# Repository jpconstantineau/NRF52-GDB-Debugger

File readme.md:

# NRF52-GDB-DEBUGGER

## Why?

### Software
This SWD Programmer gets rid of intermediate programs like OpenOCD, STLink server or Segger J-Link.  You just start GNU Debugger (GDB) and select the virtual com port offered by the programmer as your extended remote target.  This means that you only need arm-none-eabi-gdb which is part of the GNU Arm Embedded Toolchain and do not need to install any other software on your computer.  It also means that it's compatible with Windows, Linux and MacOS.

### Hardware
Hardware is compatible with the Version 1 of the [Black Magic Probe](https://github.com/blacksphere/blackmagic). Schematic of the programmer is [here](https://github.com/jpconstantineau/NRF52-GDB-Debugger/blob/master/hardware/bmp/schematic.pdf).  Although you can use an inexpensive Bluepill board and flash the BMP firmware yourself, this programmer adds these features:

* Compatible with native BMP firmware
* Supports 1.8V up to 3.3V targets (TXS0108E level shifter)
* Can provide 3.3V to the target (Mosfet switch)
* 10 pin 0.1" header compatible with the standard Arm Cortex SWD header, including the [TC2050](https://www.tag-connect.com/product/tc2050-idc-nl-10-pin-no-legs-cable-with-ribbon-connector)
* 4 pin 0.1" SWD header, compatible with the BlueMicro840 and BlueMacro840 SWD pads (No need for extra cables to flash bootloader to these boards).
* USB-C Connector

## Firmware
You can follow the instructions on the [BMP Wiki](https://github.com/blacksphere/blackmagic/wiki/Upgrading-Firmware) to update the firmware on the programmer.  You can use the latest [firmware](https://github.com/blacksphere/blackmagic/releases/) and upload the blackmagic-native.bin file contained in the tar.gz file.

On Windows, you may need [Zadig](https://github.com/pbatard/libwdi/releases/download/b730/zadig-2.5.exe) in order for the DFU Utility to detect the programmer.

## Programming the nRF52 using this programmer.

As a starting point, have a look [here](https://bluetun.serverbox.ch/2020/01/10/flashing-the-nrf52840-with-a-blackmagic-probe-swd-jtag-programmer/)

The [Community Add-on to the Adafruit_nRF52_Arduino Board Support Package](https://github.com/jpconstantineau/Community_nRF52_Arduino) has included the Black Magic Probe to the Arduino IDE so that it can be used to program the bootloader. See it in action [here](https://youtu.be/hIclx-_i-jQ)

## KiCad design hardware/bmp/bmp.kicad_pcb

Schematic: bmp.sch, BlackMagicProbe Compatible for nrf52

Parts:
C1, C2: 10uF; C_0603_1608Metric; LCSC C19702
C3, C4: 22pF; C_0603_1608Metric; LCSC C1653
C5, C6, C7, C8: 100nF; C_0603_1608Metric; LCSC C14663
D1: Green - 19-217/GHC-YR1S2/3T; LED_0603_1608Metric; LCSC C72043
D2: Red - KT-0603R; LED_0603_1608Metric; LCSC C2286
D3, D4: Yellow - 19-213/Y2C-CQ2R2L/3T(CY); LED_0603_1608Metric; LCSC C72038
J1: USB_C_Receptacle; HRO-TYPE-C-31-M-12-C165948
J2: TC2050-IDC; Tag-Connect_TC2050-IDC-NL_2x05_P1.27mm_Vertical
J3: Conn_02x05_Odd_Even; PinHeader_2x05_P2.54mm_Vertical
J4: Conn_01x03; PinHeader_1x03_P2.54mm_Vertical
J5: Conn_01x04; PinHeader_1x04_P2.54mm_Vertical
MH1, MH2: MountingHole; HOLE_JLCPCBA
Q1: SI2301CDS-T1-GE3; SOT-23; LCSC C10487
R1, R2: 5k1; R_0603_1608Metric; LCSC C23186
R3, R4: 22R; R_0603_1608Metric; LCSC C23345
R5: 1k5; R_0603_1608Metric; LCSC C22843
R7, R8, R9, R10: 1k0; R_0603_1608Metric; LCSC C21190
R11, R14, R15: 10k; R_0603_1608Metric; LCSC C25804
R12, R13: 4k7; R_0603_1608Metric; LCSC C23162
R16, R17, R18, R19, R20, R21: 100R; R_0603_1608Metric; LCSC C22775
SW2: SW_Push; SW_TACT_TS-1145A_C318904; LCSC C318904
TP1: TestPoint_Probe; KB_BlueMicro
U1: AP2112K-3.3; SOT-23-5; LCSC C51118
U2: STM32F103CBTx; LQFP-48_7x7mm_P0.5mm; LCSC C8304
U3: TXS0108EPWR; TSSOP20-0.65-6.5X4.4MM; LCSC C17206
X1: 8MHz; Crystal_SMD_5032-2Pin_5.0x3.2mm; LCSC C115962

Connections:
+3V3: C2.1, C6.1, C7.1, J2.1, Q1.2 (S), R7.2, R15.2, U1.5, U2.1 (VBAT), U2.9 (VDDA), U2.24 (VDD), U2.36 (VDD), U2.40 (PB4), U2.41 (PB5), U2.48 (VDD), U3.19
+5V: C1.1, J1.A4, R12.2, U1.1, U1.3
/BOOTLOADER: R15.1, SW2.2, U2.25 (PB12)
/LED0: R10.2, U2.20 (PB2)
/LED1: R9.2, U2.21 (PB10)
/LED2: R8.2, U2.22 (PB11)
/PWR_BB: Q1.1 (G), U2.19 (PB1)
/RST: J3.10, R21.2
/RXD: J4.2, U2.31 (PA10)
/SWCLK: J2.4, U2.37 (PA14)
/SWDIO: J2.2, U2.34 (PA13)
/TARGET_POWER_ADC: C5.1, R13.1, R14.2, U2.18 (PB0)
/TCK: J3.4, J5.3, R18.2
/TDI: J3.8, R20.2
/TDO: J3.6, R19.2
/TMS: J3.2, J5.4, R17.2
/TPWR: J3.1, J5.1, Q1.3 (D), R13.2, R16.2
/TXD: J4.1, U2.30 (PA9)
/USB_DM: R3.1, U2.32 (PA11)
/USB_DP: R4.1, U2.33 (PA12)
/USB_ENUM: R5.1, U2.29 (PA8)
/VBUS_ADC: R11.2, R12.1, U2.26 (PB13)
/iRST: U2.12 (PA2), U3.15
/iTCK: U2.15 (PA5), U3.18
/iTDI: U2.13 (PA3), U3.13
/iTDO: U2.16 (PA6), U3.12
/iTMS: U2.14 (PA4), U3.20
unnamed: C3.1, U2.5 (PD0), X1.1
unnamed: C4.1, U2.6 (PD1), X1.2
unnamed: C8.1, R16.1, U3.2, U3.10
unnamed: D1.2, R7.1
unnamed: D2.2, R8.1
unnamed: D3.2, R9.1
unnamed: D4.2, R10.1
unnamed: J1.A5, R1.2
unnamed: J1.A6, J1.B6, R4.2, R5.2
unnamed: J1.A7, J1.B7, R3.2
unnamed: J1.B5, R2.2
unnamed: R17.1, U3.1
unnamed: R18.1, U3.3
unnamed: R19.1, U3.9
unnamed: R20.1, U3.8
unnamed: R21.1, U3.6

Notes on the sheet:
VCC 1 2 TMS/SWDIO GND 3 4 TCK/SWCK GND 5 6 TDO/SWO KEY 7 8 NC/TDI NC 9 10 nRESET
Programming Interface

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
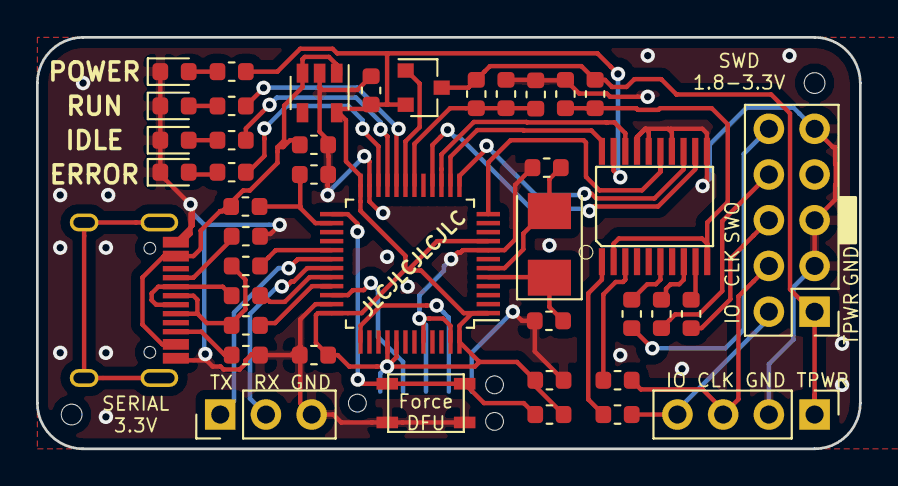
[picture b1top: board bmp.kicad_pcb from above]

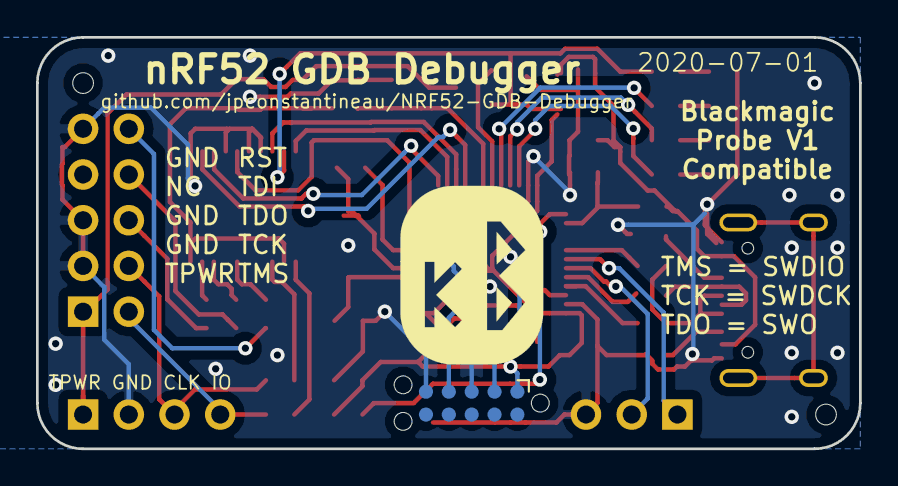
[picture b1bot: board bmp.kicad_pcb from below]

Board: 2 copper layers, 45.7 x 22.9 mm, 46 parts (2 on the bottom side), 44 nets.

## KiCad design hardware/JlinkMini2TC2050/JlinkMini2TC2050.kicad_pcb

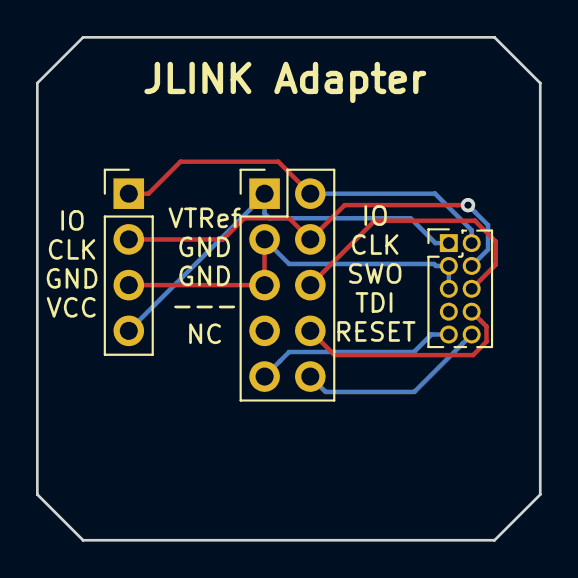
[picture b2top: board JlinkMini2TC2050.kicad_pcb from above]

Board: 2 copper layers, 27.9 x 27.9 mm, 3 parts (0 on the bottom side), 8 nets.

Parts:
J1: Conn_02x05_Odd_Even; PinHeader_2x05_P1.27mm_Vertical
J2: Conn_02x05_Odd_Even; PinHeader_2x05_P2.54mm_Vertical
J3: Conn_01x04; PinHeader_1x04_P2.54mm_Vertical

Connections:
GND: J1.3, J1.5, J2.3, J2.5, J3.3
NC: J1.9, J2.9
SWDCLK: J1.4, J2.4, J3.2
SWDIO: J1.2, J2.2, J3.1
SWO: J1.6, J2.6
TDI: J1.8, J2.8
VTRef: J1.1, J2.1, J3.4
nRESET: J1.10, J2.10

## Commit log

2020-06-27 updated scripts and native objects
2020-06-27 adding bootloader flash command
2020-06-27 adding dfu-util
2020-07-10 updated with 2019 gdb
2020-07-10 updated gitignore
2020-12-19 update to the scripts
